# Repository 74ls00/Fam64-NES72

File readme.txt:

https://www.elektroda.pl/rtvforum/topic3131101.html#15240737

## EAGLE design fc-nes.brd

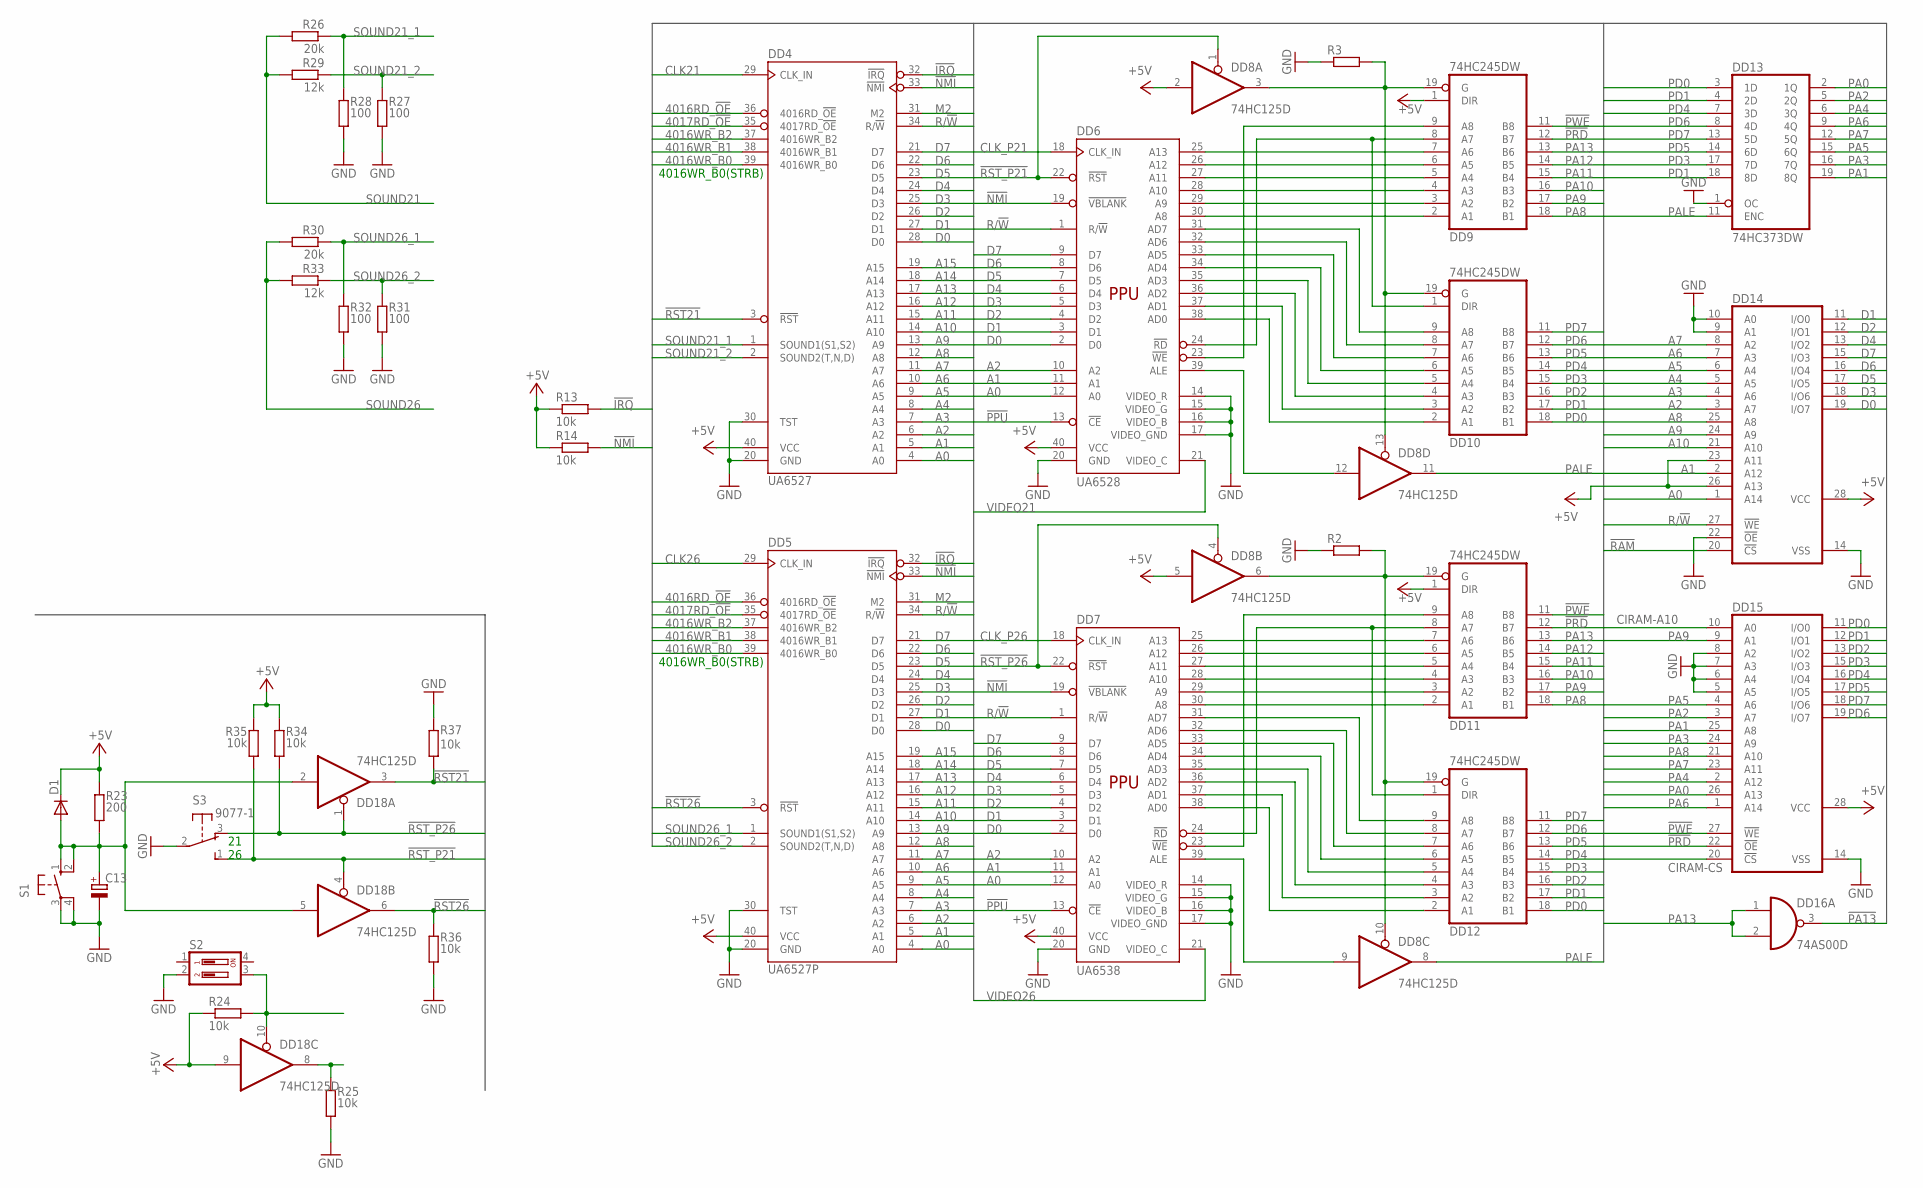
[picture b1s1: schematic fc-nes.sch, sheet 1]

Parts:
C13: CPOL-EUSMCA; SMC_A
D1: DIODE-SOD80C; SOD80C
DD4: UA6527; DIL40
DD5: UA6527P; DIL40
DD6: UA6528; DIL40
DD7: UA6538; DIL40
DD8, DD18: 74HC125D; SO14
DD9, DD10, DD11, DD12: 74HC245DW; SO20W
DD13: 74HC373DW; SO20W
DD14, DD15: 62256S; DIL28-6S
DD16: 74AS00D; SO14
R2, R3: R-EU_M0805; M0805
R13, R14, R24, R25, R34, R35, R36, R37: 10k; M0805
R23: 200; M0805
R26, R30: 20k; M0805
R27, R28, R31, R32: 100; M0805
R29, R33: 12k; M0805
S1: 10-XX; B3F-10XX
S2: DIP02YL
S3: 9077-1

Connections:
4016RD_!OE: DD4.36 (4016RD_!OE), DD5.36 (4016RD_!OE); also elsewhere on the board
4016WR_B0: DD4.39 (4016WR_B0), DD5.39 (4016WR_B0); also elsewhere on the board
4016WR_B1: DD4.38 (4016WR_B1), DD5.38 (4016WR_B1); also elsewhere on the board
4016WR_B2: DD4.37 (4016WR_B2), DD5.37 (4016WR_B2); also elsewhere on the board
4017RD_!OE: DD4.35 (4017RD_!OE), DD5.35 (4017RD_!OE); also elsewhere on the board
!IRQ: DD4.32 (!IRQ), DD5.32 (!IRQ), R13.2; also elsewhere on the board
!NMI: DD4.33 (!NMI), DD5.33 (!NMI), DD6.19 (!VBLANK), DD7.19 (!VBLANK), R14.2
!PA13: DD16.3 (O); also elsewhere on the board
!PPU: DD6.13 (!CE), DD7.13 (!CE); also elsewhere on the board
!PRD: DD9.12 (B7), DD11.12 (B7), DD15.22 (!OE); also elsewhere on the board
!PWE: DD9.11 (B8), DD11.11 (B8), DD15.27 (!WE); also elsewhere on the board
!RAM: DD14.20 (!CS); also elsewhere on the board
!RST21: DD4.3 (!RST), DD18.3 (O), R37.2
!RST26: DD5.3 (!RST), DD18.6 (O), R36.2
!RST_P21: DD6.22 (!RST), DD8.1 (OE), DD18.4 (OE), R35.1, S3.1 (S)
!RST_P26: DD7.22 (!RST), DD8.4 (OE), DD18.1 (OE), R34.1, S3.3 (O)
+5V: D1.C, DD4.40 (VCC), DD5.40 (VCC), DD6.40 (VCC), DD7.40 (VCC), DD8.2 (I), DD8.5 (I), DD9.1 (DIR), DD11.1 (DIR), DD14.23 (A11), DD14.26 (A13), DD14.28 (VCC), DD15.28 (VCC), DD18.9 (I), R13.1, R14.1, R23.2, R24.1, R34.2, R35.2; also elsewhere on the board
A0: DD4.4 (A0), DD5.4 (A0), DD6.12 (A0), DD7.12 (A0), DD14.1 (A14); also elsewhere on the board
A1: DD4.5 (A1), DD5.5 (A1), DD6.11 (A1), DD7.11 (A1), DD14.2 (A12); also elsewhere on the board
A2: DD4.6 (A2), DD5.6 (A2), DD6.10 (A2), DD7.10 (A2), DD14.3 (A7); also elsewhere on the board
A3: DD4.7 (A3), DD5.7 (A3), DD14.4 (A6); also elsewhere on the board
A4: DD4.8 (A4), DD5.8 (A4), DD14.5 (A5); also elsewhere on the board
A5: DD4.9 (A5), DD5.9 (A5), DD14.6 (A4); also elsewhere on the board
A6: DD4.10 (A6), DD5.10 (A6), DD14.7 (A3); also elsewhere on the board
A7: DD4.11 (A7), DD5.11 (A7), DD14.8 (A2); also elsewhere on the board
A8: DD4.12 (A8), DD5.12 (A8), DD14.25 (A8); also elsewhere on the board
A9: DD4.13 (A9), DD5.13 (A9), DD14.24 (A9); also elsewhere on the board
A10: DD4.14 (A10), DD5.14 (A10), DD14.21 (A10); also elsewhere on the board
A11: DD4.15 (A11), DD5.15 (A11); also elsewhere on the board
A12: DD4.16 (A12), DD5.16 (A12); also elsewhere on the board
A13: DD4.17 (A13), DD5.17 (A13); also elsewhere on the board
A14: DD4.18 (A14), DD5.18 (A14); also elsewhere on the board
A15: DD4.19 (A15), DD5.19 (A15); also elsewhere on the board
CIRAM-A10: DD15.10 (A0); also elsewhere on the board
CIRAM-CS: DD15.20 (!CS); also elsewhere on the board
CLK21: DD4.29 (CLK_IN); also elsewhere on the board
CLK26: DD5.29 (CLK_IN); also elsewhere on the board
CLK_P21: DD6.18 (CLK_IN); also elsewhere on the board
CLK_P26: DD7.18 (CLK_IN); also elsewhere on the board
D0: DD4.28 (D0), DD5.28 (D0), DD6.2 (D0), DD7.2 (D0), DD14.19 (I/O7); also elsewhere on the board
D1: DD4.27 (D1), DD5.27 (D1), DD6.3 (D1), DD7.3 (D1), DD14.11 (I/O0); also elsewhere on the board
D2: DD4.26 (D2), DD5.26 (D2), DD6.4 (D2), DD7.4 (D2), DD14.12 (I/O1); also elsewhere on the board
D3: DD4.25 (D3), DD5.25 (D3), DD6.5 (D3), DD7.5 (D3), DD14.18 (I/O6); also elsewhere on the board
D4: DD4.24 (D4), DD5.24 (D4), DD6.6 (D4), DD7.6 (D4), DD14.13 (I/O2); also elsewhere on the board
D5: DD4.23 (D5), DD5.23 (D5), DD6.7 (D5), DD7.7 (D5), DD14.17 (I/O5); also elsewhere on the board
D6: DD4.22 (D6), DD5.22 (D6), DD6.8 (D6), DD7.8 (D6), DD14.16 (I/O4); also elsewhere on the board
D7: DD4.21 (D7), DD5.21 (D7), DD6.9 (D7), DD7.9 (D7), DD14.15 (I/O3); also elsewhere on the board
GND: C13.-, DD4.20 (GND), DD4.30 (TST), DD5.20 (GND), DD5.30 (TST), DD6.14 (VIDEO_R), DD6.15 (VIDEO_G), DD6.16 (VIDEO_B), DD6.17 (VIDEO_GND), DD6.20 (GND), DD7.14 (VIDEO_R), DD7.15 (VIDEO_G), DD7.16 (VIDEO_B), DD7.17 (VIDEO_GND), DD7.20 (GND), DD13.1 (OC), DD14.9 (A1), DD14.10 (A0), DD14.14 (VSS), DD14.22 (!OE), DD15.5 (A5), DD15.6 (A4), DD15.7 (A3), DD15.8 (A2), DD15.14 (VSS), DD18.7 (GND), R2.1, R3.1, R25.1, R27.1, R28.1, R31.1, R32.1, R36.1, R37.1, S1.3, S1.4 (P1), S2.2, S3.2; also elsewhere on the board
M2: DD4.31 (M2), DD5.31 (M2); also elsewhere on the board
unnamed: DD6.23 (!WE), DD9.9 (A8)
unnamed: DD6.24 (!RD), DD9.8 (A7), DD10.1 (DIR)
unnamed: DD6.25 (A13), DD9.7 (A6)
unnamed: DD6.26 (A12), DD9.6 (A5)
unnamed: DD6.27 (A11), DD9.5 (A4)
unnamed: DD6.28 (A10), DD9.4 (A3)
unnamed: DD6.29 (A9), DD9.3 (A2)
unnamed: DD6.30 (A8), DD9.2 (A1)
unnamed: DD6.31 (AD7), DD10.9 (A8)
unnamed: DD6.32 (AD6), DD10.8 (A7)
unnamed: DD6.33 (AD5), DD10.7 (A6)
unnamed: DD6.34 (AD4), DD10.6 (A5)
unnamed: DD6.35 (AD3), DD10.5 (A4)
unnamed: DD6.36 (AD2), DD10.4 (A3)
unnamed: DD6.37 (AD1), DD10.3 (A2)
unnamed: DD6.38 (AD0), DD10.2 (A1)
unnamed: DD8.3 (O), DD8.13 (OE), DD9.19 (G), DD10.19 (G), R3.2
unnamed: DD6.39 (ALE), DD8.12 (I)
unnamed: DD7.23 (!WE), DD11.9 (A8)
unnamed: DD7.24 (!RD), DD11.8 (A7), DD12.1 (DIR)
unnamed: DD7.25 (A13), DD11.7 (A6)
unnamed: DD7.26 (A12), DD11.6 (A5)
unnamed: DD7.27 (A11), DD11.5 (A4)
unnamed: DD7.28 (A10), DD11.4 (A3)
unnamed: DD7.29 (A9), DD11.3 (A2)
unnamed: DD7.30 (A8), DD11.2 (A1)
unnamed: DD7.31 (AD7), DD12.9 (A8)
unnamed: DD7.32 (AD6), DD12.8 (A7)
unnamed: DD7.33 (AD5), DD12.7 (A6)
unnamed: DD7.34 (AD4), DD12.6 (A5)
unnamed: DD7.35 (AD3), DD12.5 (A4)
unnamed: DD7.36 (AD2), DD12.4 (A3)
unnamed: DD7.37 (AD1), DD12.3 (A2)
unnamed: DD7.38 (AD0), DD12.2 (A1)
unnamed: DD8.6 (O), DD8.10 (OE), DD11.19 (G), DD12.19 (G), R2.2
unnamed: DD7.39 (ALE), DD8.9 (I)
unnamed: C13.+, D1.A, DD18.2 (I), DD18.5 (I), R23.1, S1.1 (S), S1.2 (S1)
unnamed: DD18.10 (OE), R24.2, S2.3
unnamed: DD18.8 (O), R25.2
PA0: DD13.2 (1Q), DD15.26 (A13); also elsewhere on the board
PA1: DD13.19 (8Q), DD15.25 (A8); also elsewhere on the board
PA2: DD13.5 (2Q), DD15.3 (A7); also elsewhere on the board
PA3: DD13.16 (7Q), DD15.24 (A9); also elsewhere on the board
PA4: DD13.6 (3Q), DD15.2 (A12); also elsewhere on the board
PA5: DD13.15 (6Q), DD15.4 (A6); also elsewhere on the board
PA6: DD13.9 (4Q), DD15.1 (A14); also elsewhere on the board
PA7: DD13.12 (5Q), DD15.23 (A11); also elsewhere on the board
PA8: DD9.18 (B1), DD11.18 (B1), DD15.21 (A10); also elsewhere on the board
PA9: DD9.17 (B2), DD11.17 (B2), DD15.9 (A1); also elsewhere on the board
PA10: DD9.16 (B3), DD11.16 (B3); also elsewhere on the board
PA11: DD9.15 (B4), DD11.15 (B4); also elsewhere on the board
PA12: DD9.14 (B5), DD11.14 (B5); also elsewhere on the board
PA13: DD9.13 (B6), DD11.13 (B6), DD16.1 (I0), DD16.2 (I1); also elsewhere on the board
PALE: DD8.8 (O), DD8.11 (O), DD13.11 (ENC)
PD0: DD10.18 (B1), DD12.18 (B1), DD13.3 (1D), DD15.11 (I/O0); also elsewhere on the board
PD1: DD10.17 (B2), DD12.17 (B2), DD13.4 (2D), DD13.18 (8D), DD15.12 (I/O1); also elsewhere on the board
PD2: DD10.16 (B3), DD12.16 (B3), DD15.13 (I/O2); also elsewhere on the board
PD3: DD10.15 (B4), DD12.15 (B4), DD13.17 (7D), DD15.15 (I/O3); also elsewhere on the board
PD4: DD10.14 (B5), DD12.14 (B5), DD13.7 (3D), DD15.16 (I/O4); also elsewhere on the board
PD5: DD10.13 (B6), DD12.13 (B6), DD13.14 (6D), DD15.17 (I/O5); also elsewhere on the board
PD6: DD10.12 (B7), DD12.12 (B7), DD13.8 (4D), DD15.19 (I/O7); also elsewhere on the board
PD7: DD10.11 (B8), DD12.11 (B8), DD13.13 (5D), DD15.18 (I/O6); also elsewhere on the board
R/!W: DD4.34 (R/!W), DD5.34 (R/!W), DD6.1 (R/!W), DD7.1 (R/!W), DD14.27 (!WE); also elsewhere on the board
SOUND21: R26.2, R29.2
SOUND21_1: DD4.1 (SOUND1(S1,S2)), R26.1, R28.2
SOUND21_2: DD4.2 (SOUND2(T,N,D)), R27.2, R29.1
SOUND26: R30.2, R33.2
SOUND26_1: DD5.1 (SOUND1(S1,S2)), R30.1, R32.2
SOUND26_2: DD5.2 (SOUND2(T,N,D)), R31.2, R33.1
VCC: DD18.14 (VCC)
VIDEO21: DD6.21 (VIDEO_C)
VIDEO26: DD7.21 (VIDEO_C)

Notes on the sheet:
4016WR_B0(STRB)
21 26

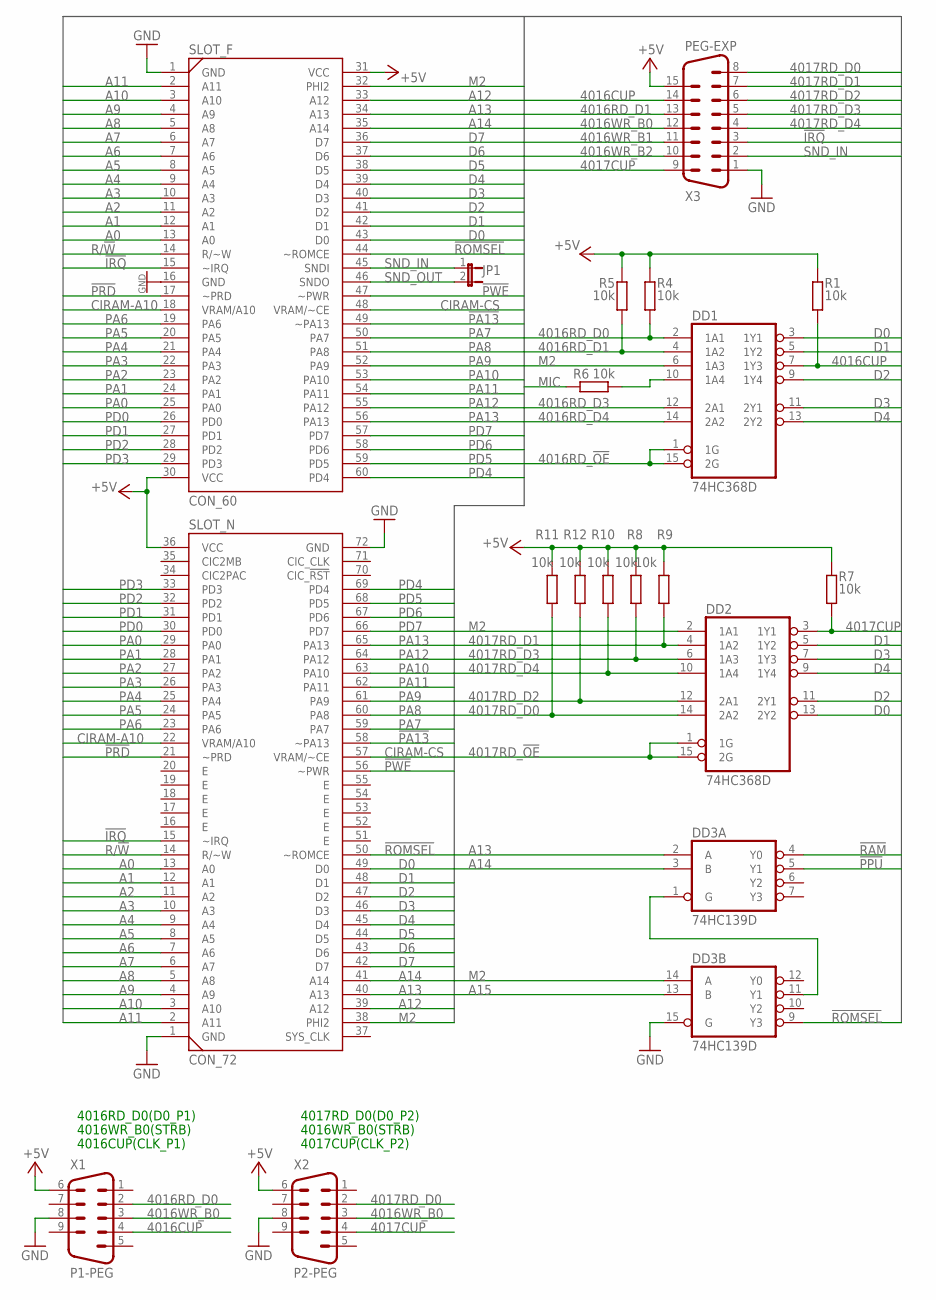
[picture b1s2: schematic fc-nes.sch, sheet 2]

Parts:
DD1, DD2: 74HC368D; SO16
DD3: 74HC139D; SO16
JP1: JP1E; JP1
R1, R4, R5, R6, R7, R8, R9, R10, R11, R12: 10k; M0805
SLOT_F: CON_60
SLOT_N: CON_72
X1: P1-PEG; M09HP
X2: P2-PEG; M09HP
X3: PEG-EXP; M15HP

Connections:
4016CUP: DD1.7 (1Y3), R1.1, X1.4, X3.14
4016RD_!OE: DD1.1 (1G), DD1.15 (2G); also elsewhere on the board
4016RD_D0: DD1.2 (1A1), R4.1, X1.2
4016RD_D1: DD1.4 (1A2), R5.1, X3.13
4016RD_D3: DD1.12 (2A1)
4016RD_D4: DD1.14 (2A2)
4016WR_B0: X1.3, X2.3, X3.12; also elsewhere on the board
4016WR_B1: X3.11; also elsewhere on the board
4016WR_B2: X3.10; also elsewhere on the board
4017CUP: DD2.3 (1Y1), R7.1, X2.4, X3.9
4017RD_!OE: DD2.1 (1G), DD2.15 (2G); also elsewhere on the board
4017RD_D0: DD2.14 (2A2), R11.2, X2.2, X3.8
4017RD_D1: DD2.4 (1A2), R9.1, X3.7
4017RD_D2: DD2.12 (2A1), R12.2, X3.6
4017RD_D3: DD2.6 (1A3), R8.1, X3.5
4017RD_D4: DD2.10 (1A4), R10.2, X3.4
!IRQ: SLOT_F.15 (~IRQ), SLOT_N.15 (~IRQ), X3.3; also elsewhere on the board
!PA13: SLOT_F.49 (~PA13), SLOT_N.58 (~PA13); also elsewhere on the board
!PPU: DD3.5 (Y1); also elsewhere on the board
!PRD: SLOT_F.17 (~PRD), SLOT_N.21 (~PRD); also elsewhere on the board
!PWE: SLOT_F.47 (~PWR), SLOT_N.56 (~PWR); also elsewhere on the board
!RAM: DD3.4 (Y0); also elsewhere on the board
!ROMSEL: DD3.9 (Y3), SLOT_F.44 (~ROMCE), SLOT_N.50 (~ROMCE)
+5V: R1.2, R4.2, R5.2, R7.2, R8.2, R9.2, R10.1, R11.1, R12.1, SLOT_F.30 (VCC), SLOT_F.31 (VCC), SLOT_N.36 (VCC), X1.6, X2.6, X3.15; also elsewhere on the board
A0: SLOT_F.13 (A0), SLOT_N.13 (A0); also elsewhere on the board
A1: SLOT_F.12 (A1), SLOT_N.12 (A1); also elsewhere on the board
A2: SLOT_F.11 (A2), SLOT_N.11 (A2); also elsewhere on the board
A3: SLOT_F.10 (A3), SLOT_N.10 (A3); also elsewhere on the board
A4: SLOT_F.9 (A4), SLOT_N.9 (A4); also elsewhere on the board
A5: SLOT_F.8 (A5), SLOT_N.8 (A5); also elsewhere on the board
A6: SLOT_F.7 (A6), SLOT_N.7 (A6); also elsewhere on the board
A7: SLOT_F.6 (A7), SLOT_N.6 (A7); also elsewhere on the board
A8: SLOT_F.5 (A8), SLOT_N.5 (A8); also elsewhere on the board
A9: SLOT_F.4 (A9), SLOT_N.4 (A9); also elsewhere on the board
A10: SLOT_F.3 (A10), SLOT_N.3 (A10); also elsewhere on the board
A11: SLOT_F.2 (A11), SLOT_N.2 (A11); also elsewhere on the board
A12: SLOT_F.33 (A12), SLOT_N.39 (A12); also elsewhere on the board
A13: DD3.2 (A), SLOT_F.34 (A13), SLOT_N.40 (A13); also elsewhere on the board
A14: DD3.3 (B), SLOT_F.35 (A14), SLOT_N.41 (A14); also elsewhere on the board
A15: DD3.13 (B); also elsewhere on the board
CIRAM-A10: SLOT_F.18 (VRAM/A10), SLOT_N.22 (VRAM/A10); also elsewhere on the board
CIRAM-CS: SLOT_F.48 (VRAM/~CE), SLOT_N.57 (VRAM/~CE); also elsewhere on the board
D0: DD1.3 (1Y1), DD2.13 (2Y2), SLOT_F.43 (D0), SLOT_N.49 (D0); also elsewhere on the board
D1: DD1.5 (1Y2), DD2.5 (1Y2), SLOT_F.42 (D1), SLOT_N.48 (D1); also elsewhere on the board
D2: DD1.9 (1Y4), DD2.11 (2Y1), SLOT_F.41 (D2), SLOT_N.47 (D2); also elsewhere on the board
D3: DD1.11 (2Y1), DD2.7 (1Y3), SLOT_F.40 (D3), SLOT_N.46 (D3); also elsewhere on the board
D4: DD1.13 (2Y2), DD2.9 (1Y4), SLOT_F.39 (D4), SLOT_N.45 (D4); also elsewhere on the board
D5: SLOT_F.38 (D5), SLOT_N.44 (D5); also elsewhere on the board
D6: SLOT_F.37 (D6), SLOT_N.43 (D6); also elsewhere on the board
D7: SLOT_F.36 (D7), SLOT_N.42 (D7); also elsewhere on the board
GND: DD3.15 (G), SLOT_F.1 (GND), SLOT_F.16 (GND), SLOT_N.1 (GND), SLOT_N.72 (GND), X1.8, X2.8, X3.1; also elsewhere on the board
M2: DD1.6 (1A3), DD2.2 (1A1), DD3.14 (A), SLOT_F.32 (PHI2), SLOT_N.38 (PHI2); also elsewhere on the board
MIC: R6.1
unnamed: DD3.1 (G), DD3.11 (Y1)
unnamed: DD1.10 (1A4), R6.2
PA0: SLOT_F.25 (PA0), SLOT_N.29 (PA0); also elsewhere on the board
PA1: SLOT_F.24 (PA1), SLOT_N.28 (PA1); also elsewhere on the board
PA2: SLOT_F.23 (PA2), SLOT_N.27 (PA2); also elsewhere on the board
PA3: SLOT_F.22 (PA3), SLOT_N.26 (PA3); also elsewhere on the board
PA4: SLOT_F.21 (PA4), SLOT_N.25 (PA4); also elsewhere on the board
PA5: SLOT_F.20 (PA5), SLOT_N.24 (PA5); also elsewhere on the board
PA6: SLOT_F.19 (PA6), SLOT_N.23 (PA6); also elsewhere on the board
PA7: SLOT_F.50 (PA7), SLOT_N.59 (PA7); also elsewhere on the board
PA8: SLOT_F.51 (PA8), SLOT_N.60 (PA8); also elsewhere on the board
PA9: SLOT_F.52 (PA9), SLOT_N.61 (PA9); also elsewhere on the board
PA10: SLOT_F.53 (PA10), SLOT_N.63 (PA10); also elsewhere on the board
PA11: SLOT_F.54 (PA11), SLOT_N.62 (PA11); also elsewhere on the board
PA12: SLOT_F.55 (PA12), SLOT_N.64 (PA12); also elsewhere on the board
PA13: SLOT_F.56 (PA13), SLOT_N.65 (PA13); also elsewhere on the board
PD0: SLOT_F.26 (PD0), SLOT_N.30 (PD0); also elsewhere on the board
PD1: SLOT_F.27 (PD1), SLOT_N.31 (PD1); also elsewhere on the board
PD2: SLOT_F.28 (PD2), SLOT_N.32 (PD2); also elsewhere on the board
PD3: SLOT_F.29 (PD3), SLOT_N.33 (PD3); also elsewhere on the board
PD4: SLOT_F.60 (PD4), SLOT_N.69 (PD4); also elsewhere on the board
PD5: SLOT_F.59 (PD5), SLOT_N.68 (PD5); also elsewhere on the board
PD6: SLOT_F.58 (PD6), SLOT_N.67 (PD6); also elsewhere on the board
PD7: SLOT_F.57 (PD7), SLOT_N.66 (PD7); also elsewhere on the board
R/!W: SLOT_F.14 (R/~W), SLOT_N.14 (R/~W); also elsewhere on the board
SND_IN: JP1.1, SLOT_F.45 (SNDI), X3.2
SND_OUT: JP1.2, SLOT_F.46 (SNDO)

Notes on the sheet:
4016RD_D0(D0_P1)
4016WR_B0(STRB)
4017RD_D0(D0_P2)
4017CUP(CLK_P2)
4016CUP(CLK_P1)

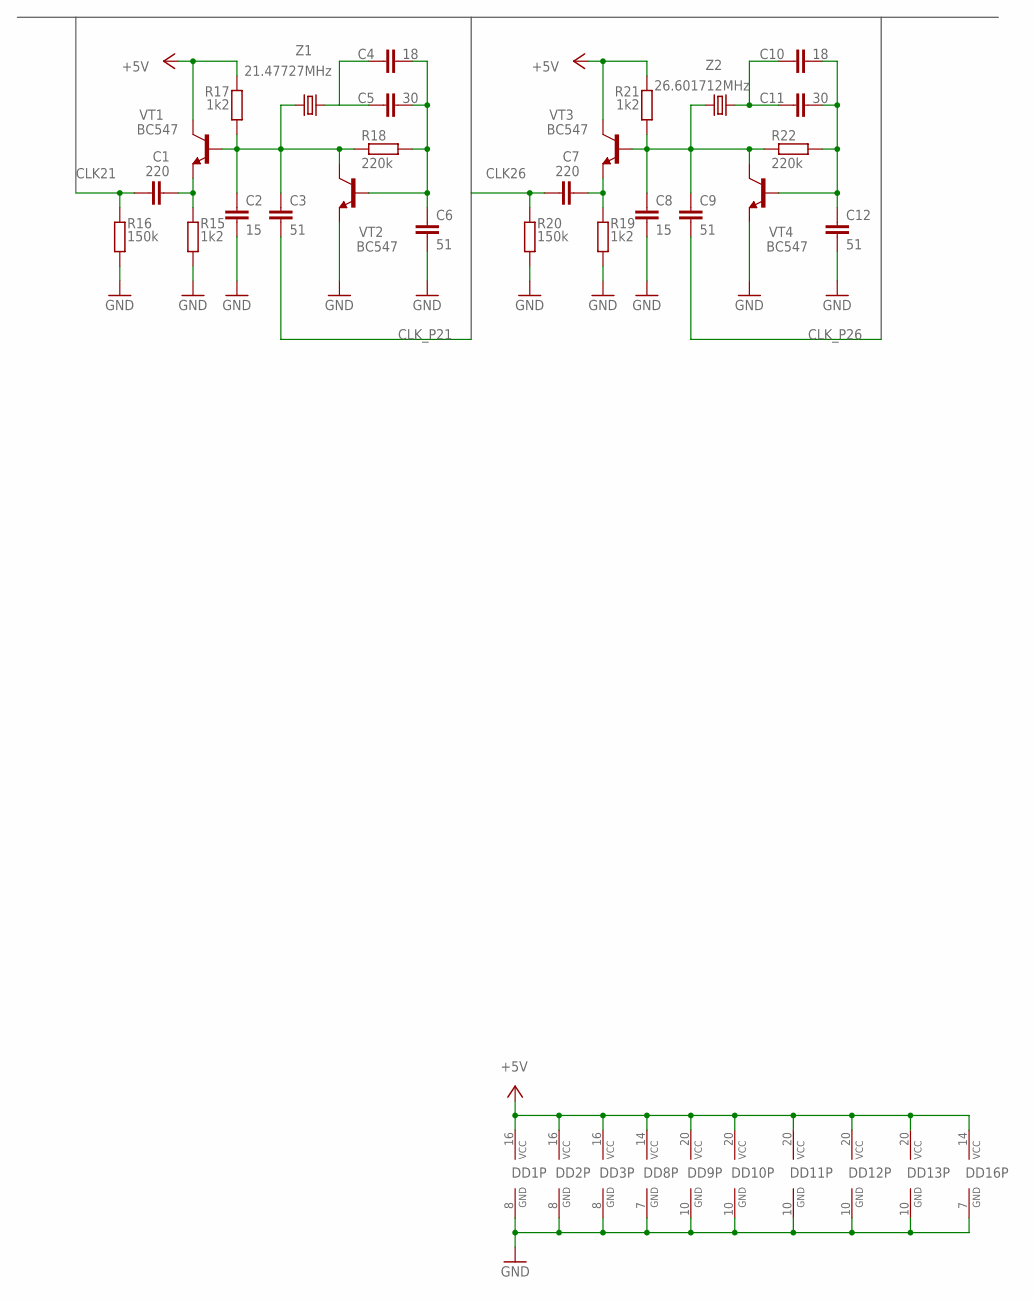
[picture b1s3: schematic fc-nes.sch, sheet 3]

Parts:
C1, C7: 220; C0805
C2, C8: 15; C0805
C3, C6, C9, C12: 51; C0805
C4, C10: 18; C0805
C5, C11: 30; C0805
DD1, DD2: 74HC368D; SO16
DD3: 74HC139D; SO16
DD8: 74HC125D; SO14
DD9, DD10, DD11, DD12: 74HC245DW; SO20W
DD13: 74HC373DW; SO20W
DD16: 74AS00D; SO14
R15, R17, R19, R21: 1k2; M0805
R16, R20: 150k; M0805
R18, R22: 220k; M0805
VT1, VT2, VT3, VT4: BC547; TO92-CBE
Z1: 21.47727MHz; HC49/S
Z2: 26.601712MHz; HC49/S

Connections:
+5V: DD1.16 (VCC), DD2.16 (VCC), DD3.16 (VCC), DD8.14 (VCC), DD9.20 (VCC), DD10.20 (VCC), DD11.20 (VCC), DD12.20 (VCC), DD13.20 (VCC), DD16.14 (VCC), R17.2, R21.2, VT1.C, VT3.C; also elsewhere on the board
CLK21: C1.1, R16.2; also elsewhere on the board
CLK26: C7.1, R20.2; also elsewhere on the board
CLK_P21: C3.2; also elsewhere on the board
CLK_P26: C9.2; also elsewhere on the board
GND: C2.2, C6.2, C8.2, C12.2, DD1.8 (GND), DD2.8 (GND), DD3.8 (GND), DD8.7 (GND), DD9.10 (GND), DD10.10 (GND), DD11.10 (GND), DD12.10 (GND), DD13.10 (GND), DD16.7 (GND), R15.1, R16.1, R19.1, R20.1, VT2.E, VT4.E; also elsewhere on the board
unnamed: C1.2, R15.2, VT1.E
unnamed: C7.2, R19.2, VT3.E
unnamed: C2.1, C3.1, R17.1, R18.1, VT1.B, VT2.C, Z1.1
unnamed: C4.2, C5.2, C6.1, R18.2, VT2.B
unnamed: C8.1, C9.1, R21.1, R22.1, VT3.B, VT4.C, Z2.1
unnamed: C4.1, C5.1, Z1.2
unnamed: C10.1, C11.1, Z2.2
unnamed: C10.2, C11.2, C12.1, R22.2, VT4.B

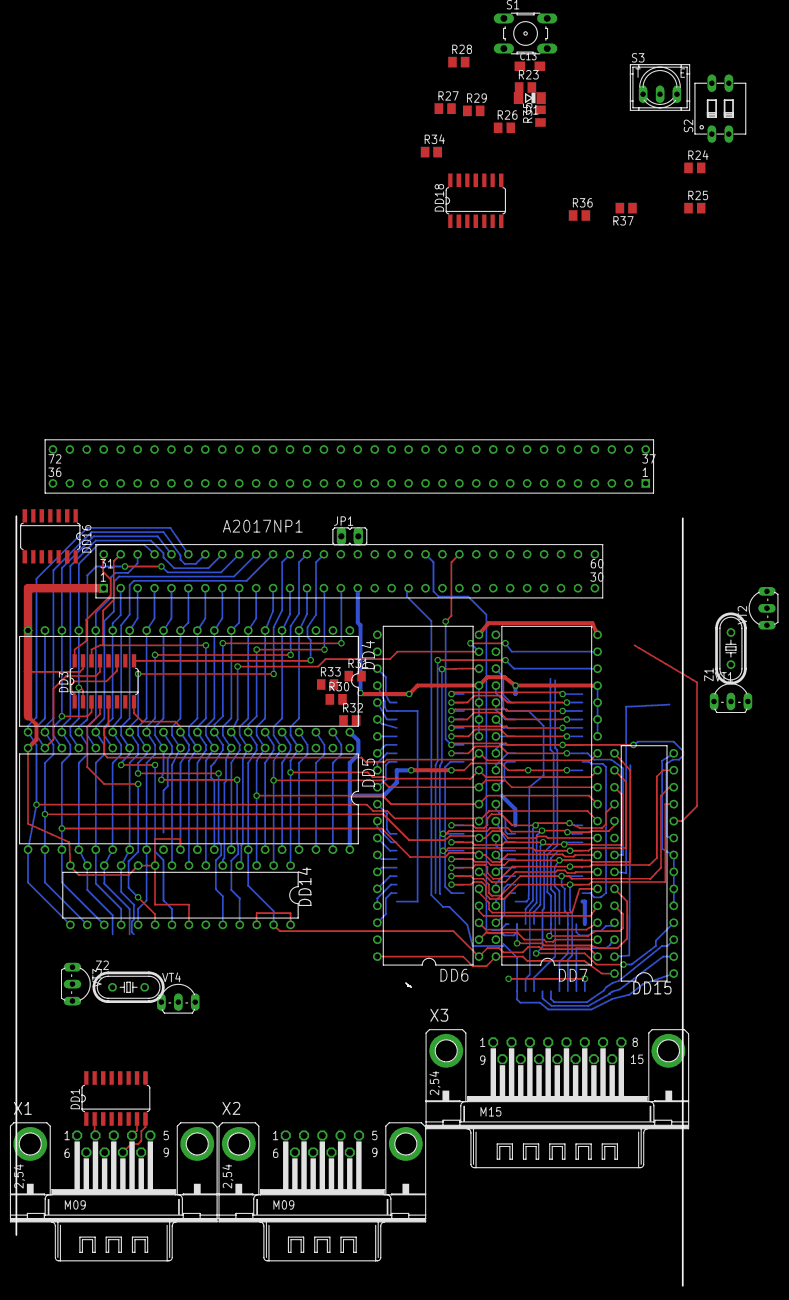
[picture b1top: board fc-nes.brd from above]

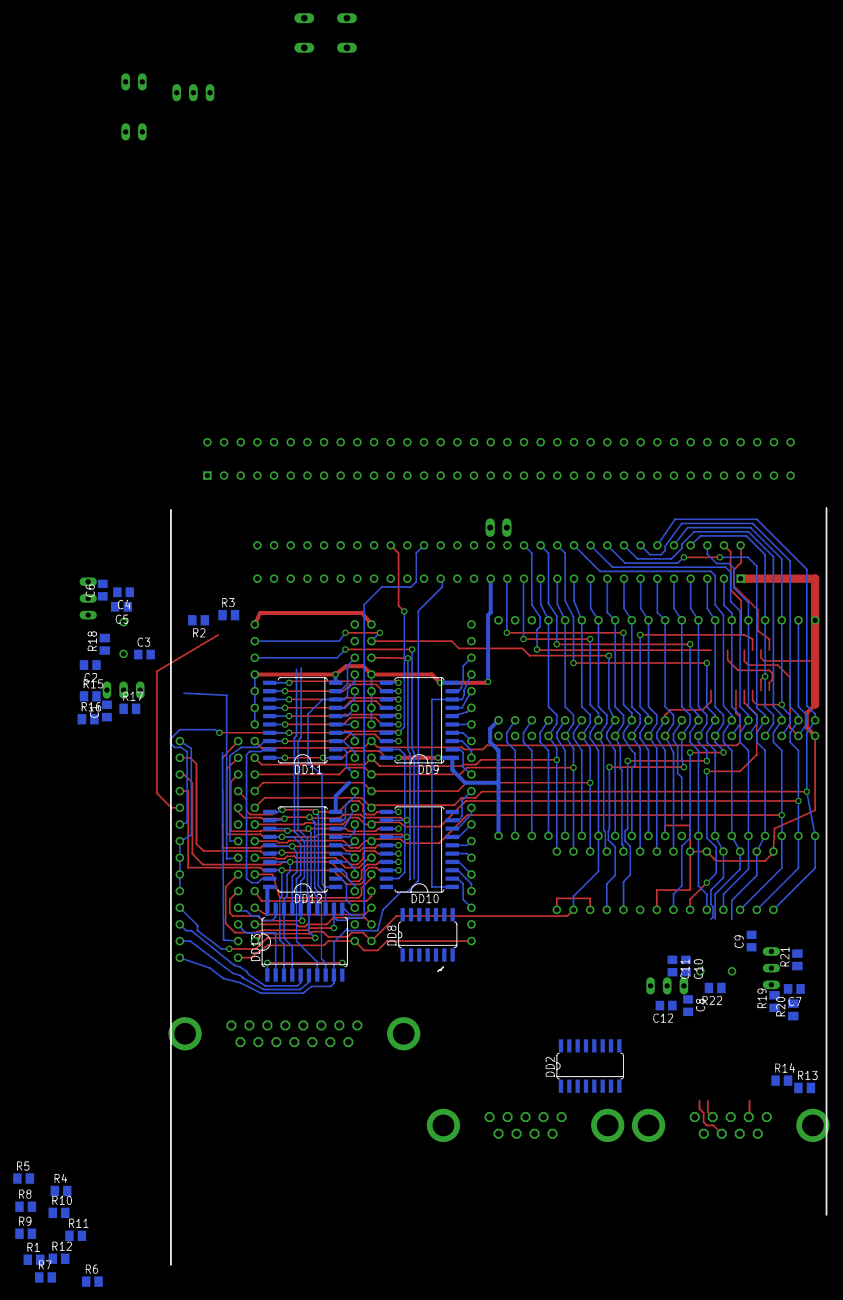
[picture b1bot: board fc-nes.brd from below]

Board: 2 copper layers, 83 parts (41 on the bottom side), 140 nets.

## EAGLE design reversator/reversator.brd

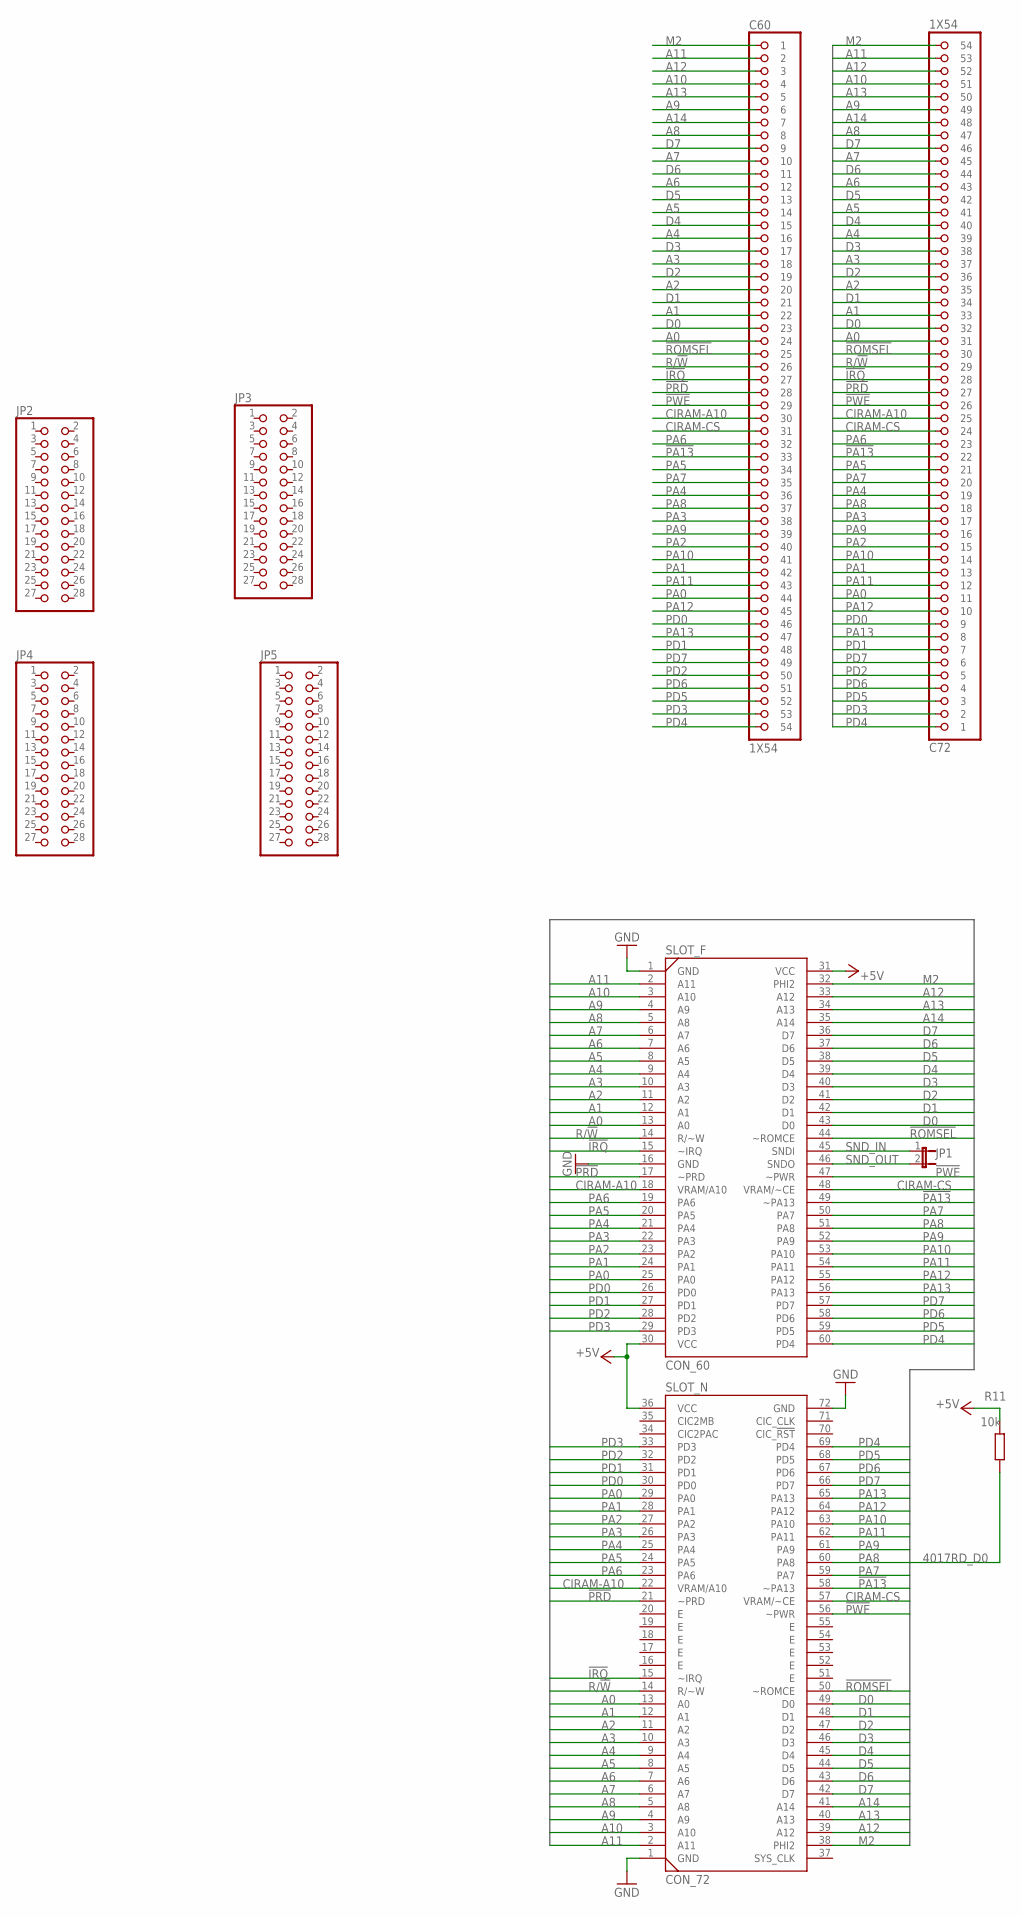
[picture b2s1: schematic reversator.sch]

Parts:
C60, C72: 1X54
JP1: JP1E; JP1
JP2, JP3, JP4, JP5: PINHD-2X14; 2X14
R11: 10k; M0805
SLOT_F: CON_60
SLOT_N: CON_72

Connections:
4017RD_D0: R11.2
!IRQ: C60.P$27 (27), C72.P$28 (28), SLOT_F.15 (~IRQ), SLOT_N.15 (~IRQ)
!PA13: C60.P$33 (33), C72.P$22 (22), SLOT_F.49 (~PA13), SLOT_N.58 (~PA13)
!PRD: C60.P$28 (28), C72.P$27 (27), SLOT_F.17 (~PRD), SLOT_N.21 (~PRD)
!PWE: C60.P$29 (29), C72.P$26 (26), SLOT_F.47 (~PWR), SLOT_N.56 (~PWR)
!ROMSEL: C60.P$25 (25), C72.P$30 (30), SLOT_F.44 (~ROMCE), SLOT_N.50 (~ROMCE)
+5V: R11.1, SLOT_F.30 (VCC), SLOT_F.31 (VCC), SLOT_N.36 (VCC)
A0: C60.P$24 (24), C72.P$31 (31), SLOT_F.13 (A0), SLOT_N.13 (A0)
A1: C60.P$22 (22), C72.P$33 (33), SLOT_F.12 (A1), SLOT_N.12 (A1)
A2: C60.P$20 (20), C72.P$35 (35), SLOT_F.11 (A2), SLOT_N.11 (A2)
A3: C60.P$18 (18), C72.P$37 (37), SLOT_F.10 (A3), SLOT_N.10 (A3)
A4: C60.P$16 (16), C72.P$39 (39), SLOT_F.9 (A4), SLOT_N.9 (A4)
A5: C60.P$14 (14), C72.P$41 (41), SLOT_F.8 (A5), SLOT_N.8 (A5)
A6: C60.P$12 (12), C72.P$43 (43), SLOT_F.7 (A6), SLOT_N.7 (A6)
A7: C60.P$10 (10), C72.P$45 (45), SLOT_F.6 (A7), SLOT_N.6 (A7)
A8: C60.P$8 (8), C72.P$47 (47), SLOT_F.5 (A8), SLOT_N.5 (A8)
A9: C60.P$6 (6), C72.P$49 (49), SLOT_F.4 (A9), SLOT_N.4 (A9)
A10: C60.P$4 (4), C72.P$51 (51), SLOT_F.3 (A10), SLOT_N.3 (A10)
A11: C60.P$2 (2), C72.P$53 (53), SLOT_F.2 (A11), SLOT_N.2 (A11)
A12: C60.P$3 (3), C72.P$52 (52), SLOT_F.33 (A12), SLOT_N.39 (A12)
A13: C60.P$5 (5), C72.P$50 (50), SLOT_F.34 (A13), SLOT_N.40 (A13)
A14: C60.P$7 (7), C72.P$48 (48), SLOT_F.35 (A14), SLOT_N.41 (A14)
CIRAM-A10: C60.P$30 (30), C72.P$25 (25), SLOT_F.18 (VRAM/A10), SLOT_N.22 (VRAM/A10)
CIRAM-CS: C60.P$31 (31), C72.P$24 (24), SLOT_F.48 (VRAM/~CE), SLOT_N.57 (VRAM/~CE)
D0: C60.P$23 (23), C72.P$32 (32), SLOT_F.43 (D0), SLOT_N.49 (D0)
D1: C60.P$21 (21), C72.P$34 (34), SLOT_F.42 (D1), SLOT_N.48 (D1)
D2: C60.P$19 (19), C72.P$36 (36), SLOT_F.41 (D2), SLOT_N.47 (D2)
D3: C60.P$17 (17), C72.P$38 (38), SLOT_F.40 (D3), SLOT_N.46 (D3)
D4: C60.P$15 (15), C72.P$40 (40), SLOT_F.39 (D4), SLOT_N.45 (D4)
D5: C60.P$13 (13), C72.P$42 (42), SLOT_F.38 (D5), SLOT_N.44 (D5)
D6: C60.P$11 (11), C72.P$44 (44), SLOT_F.37 (D6), SLOT_N.43 (D6)
D7: C60.P$9 (9), C72.P$46 (46), SLOT_F.36 (D7), SLOT_N.42 (D7)
GND: SLOT_F.1 (GND), SLOT_F.16 (GND), SLOT_N.1 (GND), SLOT_N.72 (GND)
M2: C60.P$1 (1), C72.P$54 (54), SLOT_F.32 (PHI2), SLOT_N.38 (PHI2)
PA0: C60.P$44 (44), C72.P$11 (11), SLOT_F.25 (PA0), SLOT_N.29 (PA0)
PA1: C60.P$42 (42), C72.P$13 (13), SLOT_F.24 (PA1), SLOT_N.28 (PA1)
PA2: C60.P$40 (40), C72.P$15 (15), SLOT_F.23 (PA2), SLOT_N.27 (PA2)
PA3: C60.P$38 (38), C72.P$17 (17), SLOT_F.22 (PA3), SLOT_N.26 (PA3)
PA4: C60.P$36 (36), C72.P$19 (19), SLOT_F.21 (PA4), SLOT_N.25 (PA4)
PA5: C60.P$34 (34), C72.P$21 (21), SLOT_F.20 (PA5), SLOT_N.24 (PA5)
PA6: C60.P$32 (32), C72.P$23 (23), SLOT_F.19 (PA6), SLOT_N.23 (PA6)
PA7: C60.P$35 (35), C72.P$20 (20), SLOT_F.50 (PA7), SLOT_N.59 (PA7)
PA8: C60.P$37 (37), C72.P$18 (18), SLOT_F.51 (PA8), SLOT_N.60 (PA8)
PA9: C60.P$39 (39), C72.P$16 (16), SLOT_F.52 (PA9), SLOT_N.61 (PA9)
PA10: C60.P$41 (41), C72.P$14 (14), SLOT_F.53 (PA10), SLOT_N.63 (PA10)
PA11: C60.P$43 (43), C72.P$12 (12), SLOT_F.54 (PA11), SLOT_N.62 (PA11)
PA12: C60.P$45 (45), C72.P$10 (10), SLOT_F.55 (PA12), SLOT_N.64 (PA12)
PA13: C60.P$47 (47), C72.P$8 (8), SLOT_F.56 (PA13), SLOT_N.65 (PA13)
PD0: C60.P$46 (46), C72.P$9 (9), SLOT_F.26 (PD0), SLOT_N.30 (PD0)
PD1: C60.P$48 (48), C72.P$7 (7), SLOT_F.27 (PD1), SLOT_N.31 (PD1)
PD2: C60.P$50 (50), C72.P$5 (5), SLOT_F.28 (PD2), SLOT_N.32 (PD2)
PD3: C60.P$53 (53), C72.P$2 (2), SLOT_F.29 (PD3), SLOT_N.33 (PD3)
PD4: C60.P$54 (54), C72.P$1 (1), SLOT_F.60 (PD4), SLOT_N.69 (PD4)
PD5: C60.P$52 (52), C72.P$3 (3), SLOT_F.59 (PD5), SLOT_N.68 (PD5)
PD6: C60.P$51 (51), C72.P$4 (4), SLOT_F.58 (PD6), SLOT_N.67 (PD6)
PD7: C60.P$49 (49), C72.P$6 (6), SLOT_F.57 (PD7), SLOT_N.66 (PD7)
R/!W: C60.P$26 (26), C72.P$29 (29), SLOT_F.14 (R/~W), SLOT_N.14 (R/~W)
SND_IN: JP1.1, SLOT_F.45 (SNDI)
SND_OUT: JP1.2, SLOT_F.46 (SNDO)

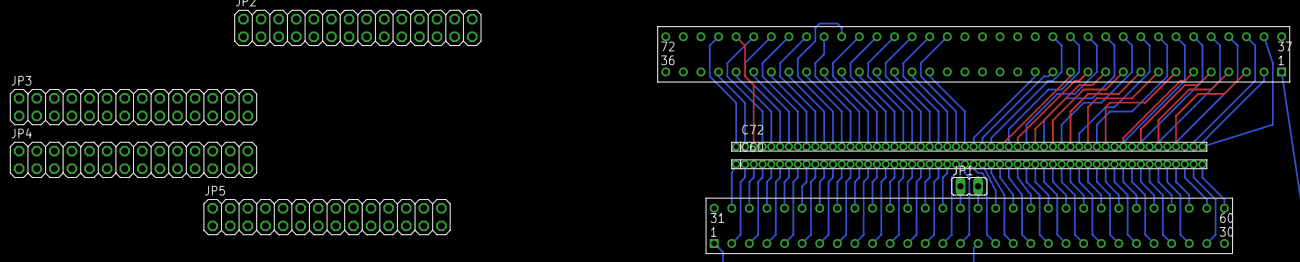
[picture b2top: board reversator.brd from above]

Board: 2 copper layers, 10 parts (1 on the bottom side), 58 nets.
